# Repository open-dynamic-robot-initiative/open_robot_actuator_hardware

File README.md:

# Open Robot Actuator Hardware

**Click on the pictures below for more information**
## Electronics
| TI Evaluation Boards  | BLMC µDriver | Master Board |Details Wiring|
| ---------------  | ------------- |------------- |---|
| |   |   | |

## Mechanics
| Quadruped 8dof v2 (Solo8) | Quadruped 12dof (Solo12) | Biped 6dof (Bolt) | TriFingerEdu |
| ------------------------- | ------------- |------------- |------------- |
|||||

| 2dof Leg v2  | 3dof Leg | Biped Leg |FingerEdu |
| ------------- | ------------- |------------- |------------- |
|   |   |   |  |

| Actuator Module Core v1| Actuator Module Core v1.1 | Details 3d Printed Parts | Details Machined Parts |
| ---------------  | ------------- |------------- |------------- |
| |  | |  |

| Quadruped 12dof v1.1<br>Autonomy Upgrade | Leg Test Stand v2 | NYU Finger | Dual Motor Testbed |
| ---------------  | ------------- |------------- |-----------|
| |  |  |  |

## More Details
| Mechanical Tools and Consumables |Electronic Components and Tools| Details Electronics<br>Quadruped Robot 12dof | Lower Legs |
| --- | --- | --- |--- |
|||  |   |

| Robot Calibration | Conventions | Known Issues |  |
| --- | --- | --- | --- |
|||||

## Step-by-Step Instructions
| Motor Preparation  | Motor Shaft Preparation | Encoder Preparation |Center Pulley Preparation|
| --- | --- | --- | --- |
| |   |   | |

| Output Pulley Preparation | Shell Preparation | Actuator Module Assembly |Actuator Module Testing|
| --- | --- | --- | --- |
| |   |   | |

## Old Versions for Reference
| Quadruped 8dof v1 | 2dof Leg v1 | Leg Test Stand v1| Foot Contact Switch |
| ---------------  | ------------- |------------- |------------- |
| | |||

## More Information
[Open Dynamic Robot Initiative - Webpage](https://open-dynamic-robot-initiative.github.io)  
[Open Dynamic Robot Initiative - YouTube Channel](https://www.youtube.com/channel/UCx32JW2oIrax47Gjq8zNI-w)   
[Open Dynamic Robot Initiative - Forum](https://odri.discourse.group/categories)  
[Open Dynamic Robot Initiative - Paper](https://arxiv.org/pdf/1910.00093.pdf)  
[Hardware Overview](#open-robot-actuator-hardware)  
[Software Overview](https://github.com/open-dynamic-robot-initiative/open-dynamic-robot-initiative.github.io/wiki)  

## Authors
Jonathan Fiene  
Thomas Flayols  
Felix Grimminger  

## License
BSD 3-Clause License

## Copyright
Copyright (c) 2019-2021, Max Planck Gesellschaft and New York University

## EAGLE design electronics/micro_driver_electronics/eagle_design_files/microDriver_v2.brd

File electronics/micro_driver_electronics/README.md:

# Micro Driver Electronics

<br> <br>

* dual brushless motor driver electronics
* performs torque control at 10kHz for each motor
* miniaturized version of the [Texas Instruments Evaluation Boards](../ti_electronics/README.md#texas-instruments-evaluation-board-electronics)
* SPI communication with [Master Board](https://github.com/open-dynamic-robot-initiative/master-board#master-board) at 1kHz
* 6 layer board / FR4 / copper thickness 35μm
* Dimensions: 51mm x 50mm
* Weight: 13g
* input voltage: 5V - 32V (we operate our robots at 24V)

## LED status
GREEN/BLUE LED (shows system and motor status):<br>
Off = system disabled<br>
On =system enabled<br>
Slow Blinking = motor enabled<br>
Fast Blinking = aligning motor<br>

RED LED: Turn on if there is an error

## Motor Driver Electronics Comparison
<br> <br>

## Eagle Design Files
<br>

* [MicroDriver v2 Eagle Design Files - microDriver_v2.zip](eagle_design_files/microDriver_v2.zip)

<br><br> <br>

---
## Production Gerber Set and Assembly Packet
* [MicroDriver v2 Gerber Set - microDriver_v2_gerber.zip](production_files/microDriver_v2_gerber.zip)

* [MicroDriver v2 Assembly Packet - microDriver_v2_assembly.zip](production_files/microDriver_v2_assembly.zip)

<br><br> <br>

## Ordering Instructions
### Beta Layout
We have mostly been ordering the Micro Driver boards from [BetaLayout](https://us.beta-layout.com/pcb/).
Beta Layout has the permission to replicate our MicroDriver v2 board order for anybody who is interested - they ship worldwide.

Send an email to info.de@beta-layout.com and ask for a quote for replicating the MicroDriver v2 boards according to the order number **AU-201909/38760**.

They will send you a quote for producing the boards and for the placing and soldering service *- NOT including the cost of the electronic components.*

After you have placed the order for the boards Beta Layout will search for the components and will send you the component list with the actual component prices for your approval. For our last orders the component price was around 50€ per board.

We order the boards with all the components placed and soldered - except for the precision resistors and the Hirose connectors. The soldering of those components is described [below](#soldering-work).

### MacroFab

In the US we have also successfully ordered the Micro Driver Boards from [MacroFab](https://macrofab.com/).

---
## Bill of Materials
### Micro Driver Boards
<br> <br>

|Description|Details|Ordering Information|Comments|
|---|---|---|---|
|MicroDriver v2||[BetaLayout](https://us.beta-layout.com/pcb/)<br> USA: [MacroFab](https://macrofab.com/)|[Ordering Instructions](#ordering-instructions)|
|Precision Resistors 7mΩ ±1%|CRE2512-FZ-R007E-3|RS 824-0348<br>Mouser 652-CRE2512FZR007E-3 |Phase Current Measurement Micro Driver Board|
|Right Angle Pin Header|Pitch 2.54mm|RS 360-6364 |Motor Phase and Power Connection Micro Driver Board|
|Hirose DF13 Right Angle Header 5 Pin|DF13-5P-1.25DS(20)|Digi-Key H2202-ND|Encoder and SPI connector Micro Driver Board. We use the [right angle connectors](../details/details_components.md#hirose-df13-right-angle-pin-headers). Alternatively you can use the [straight connectors](../details/details_components.md#hirose-df13-straight-pin-headers).|

### Flash Adapter and Flash Wire
<br> <br>

|Description|Details|Ordering Information|Comments|
|---|---|---|---|
|JTAG EMULATOR XDS100V2 USB|Spectrum Digital XDS100V2 JTAG|Digi Key 702302-ND<br> Farnell 1831927||
|Pin Header 8 Position 1.27mm pitch|Amphenol ICC 20021111-00008T4LF|Digi-Key 609-3711-ND|Flash Cable Connector Micro Driver Side|
|Pin Header 2,54 mm pitch|Assmann AWL254-DG-G72A|RS 674-2347|Flash Cable Connector Emulator Side|
|Ribbon Cable|HARTING 09180107001|DigiKey 1195-4452-ND|Pitch 1,27mm / 0,050" |

---
# Soldering Work

The MicroDrivers come without any connectors (for power wires, encoders, spi and motor wires). These have to been added. In addition, six resistors have to been soldered on the back of the MicroDriver.

For the encoder connectors, it's possible to use either [Hirose DF13 Straight Pin Headers](../details/details_components.md#hirose-df13-straight-pin-headers) or the [Hirose DF13 Right Angle Pin Headers](../details/details_components.md#hirose-df13-right-angle-pin-headers)

## Resistor Soldering
The six [precision resistors](../details/details_components.md#precision-resistors) needs to be soldered on the back of the MicroDriver.<br>
**Trick:** Use some solder at the tip to initially fix the resistor a bit. Then solder the other side and fix the initial side in the end properly.

<br>

<br>

<br>

## Hirose Connector Soldering

<br>*Micro Driver Stack with right angle Hirose connectors.*<br>

We recommend to use the right angle Hirose connectors for the encoders and the SPI communication if the cards are mounted in a stack. This allows for connecting and disconnecting the encoder and SPI wires without disassembling the stack.

The **right angle Hirose connectors** are mounted to the **bottom side** of the micro driver boards as shown in the picture below.
The **straight Hirose connectors** are mounted on the **top side** of the micro driver boards. That way the pin assignment is identical and both connector options are compatible with the [Actuator Module Wiring Interface](../details/details_wiring.md#actuator-module-wiring).

<br>*Micro Driver Boards with Hirose encoder connectors.<br>Left side: right angle connectors / Right side: straight connectors*<br>

<br>*Micro Driver Boards with Hirose connector for SPI communication.<br>Left side: right angle connectors / Right side: straight connectors*<br>

<br>*Use a vise to clamp the board and locate the Hirose connector.*<br>

<br>*Solder the two encoder connectors and the spi connector onto the board.*<br>

## Motor / Power Wire Soldering

<br>*Solder a two pin right angle connector to the power terminals.*<br>

<br>*Shorten the pins, solder the extension wires and apply heat shrink.*<br>

<br>*Right angle pin and mating connector.*<br>

<br>*Use a mating connector to hold the pin during soldering.*<br>

<br>*Orient the pin as desired, apply solder and shorten the pins.*<br>

<br>*Repeat for all six motor phase connections.*<br>

<br>*Apply the extension wires and heat shrink.*<br>

<br>*Attach the [2mm motor phase connectors](../details/details_components.md#motor-phase-connectors) and label the wires.<br>On one of the boards we attach a 2 pin Hirose wire to power the Master Board.*<br>

---
## Flashing

The MicroDriver boards are flashed using a JTAG emulator connected via USB.<br> The emulator is connected to the MicroDriver using the connector cable described below.

## Wiring MicroDriver <-> JTAG Emulator

Note: A long wire might cause communication problems when attempting to flash the MicroDriver. A cable length of 10 cm worked well for us.

| Connector Emulator | Connector MicroDriver |
|--------------------|-----------------------|
|  |  |

---
## More Information
[Open Dynamic Robot Initiative - Webpage](https://open-dynamic-robot-initiative.github.io)  
[Open Dynamic Robot Initiative - YouTube Channel](https://www.youtube.com/channel/UCx32JW2oIrax47Gjq8zNI-w)  
[Open Dynamic Robot Initiative - Forum](https://odri.discourse.group/categories)  
[Open Dynamic Robot Initiative - Paper](https://arxiv.org/pdf/1910.00093.pdf)  
[Hardware Overview](../../README.md#open-robot-actuator-hardware)  
[Software Overview](https://github.com/open-dynamic-robot-initiative/open-dynamic-robot-initiative.github.io/wiki)

## Authors
* Jonathan Fiene
* Julian Viereck
* Felix Grimminger

## License
BSD 3-Clause License

## Copyright
Copyright (c) 2019-2021, Max Planck Gesellschaft and New York University

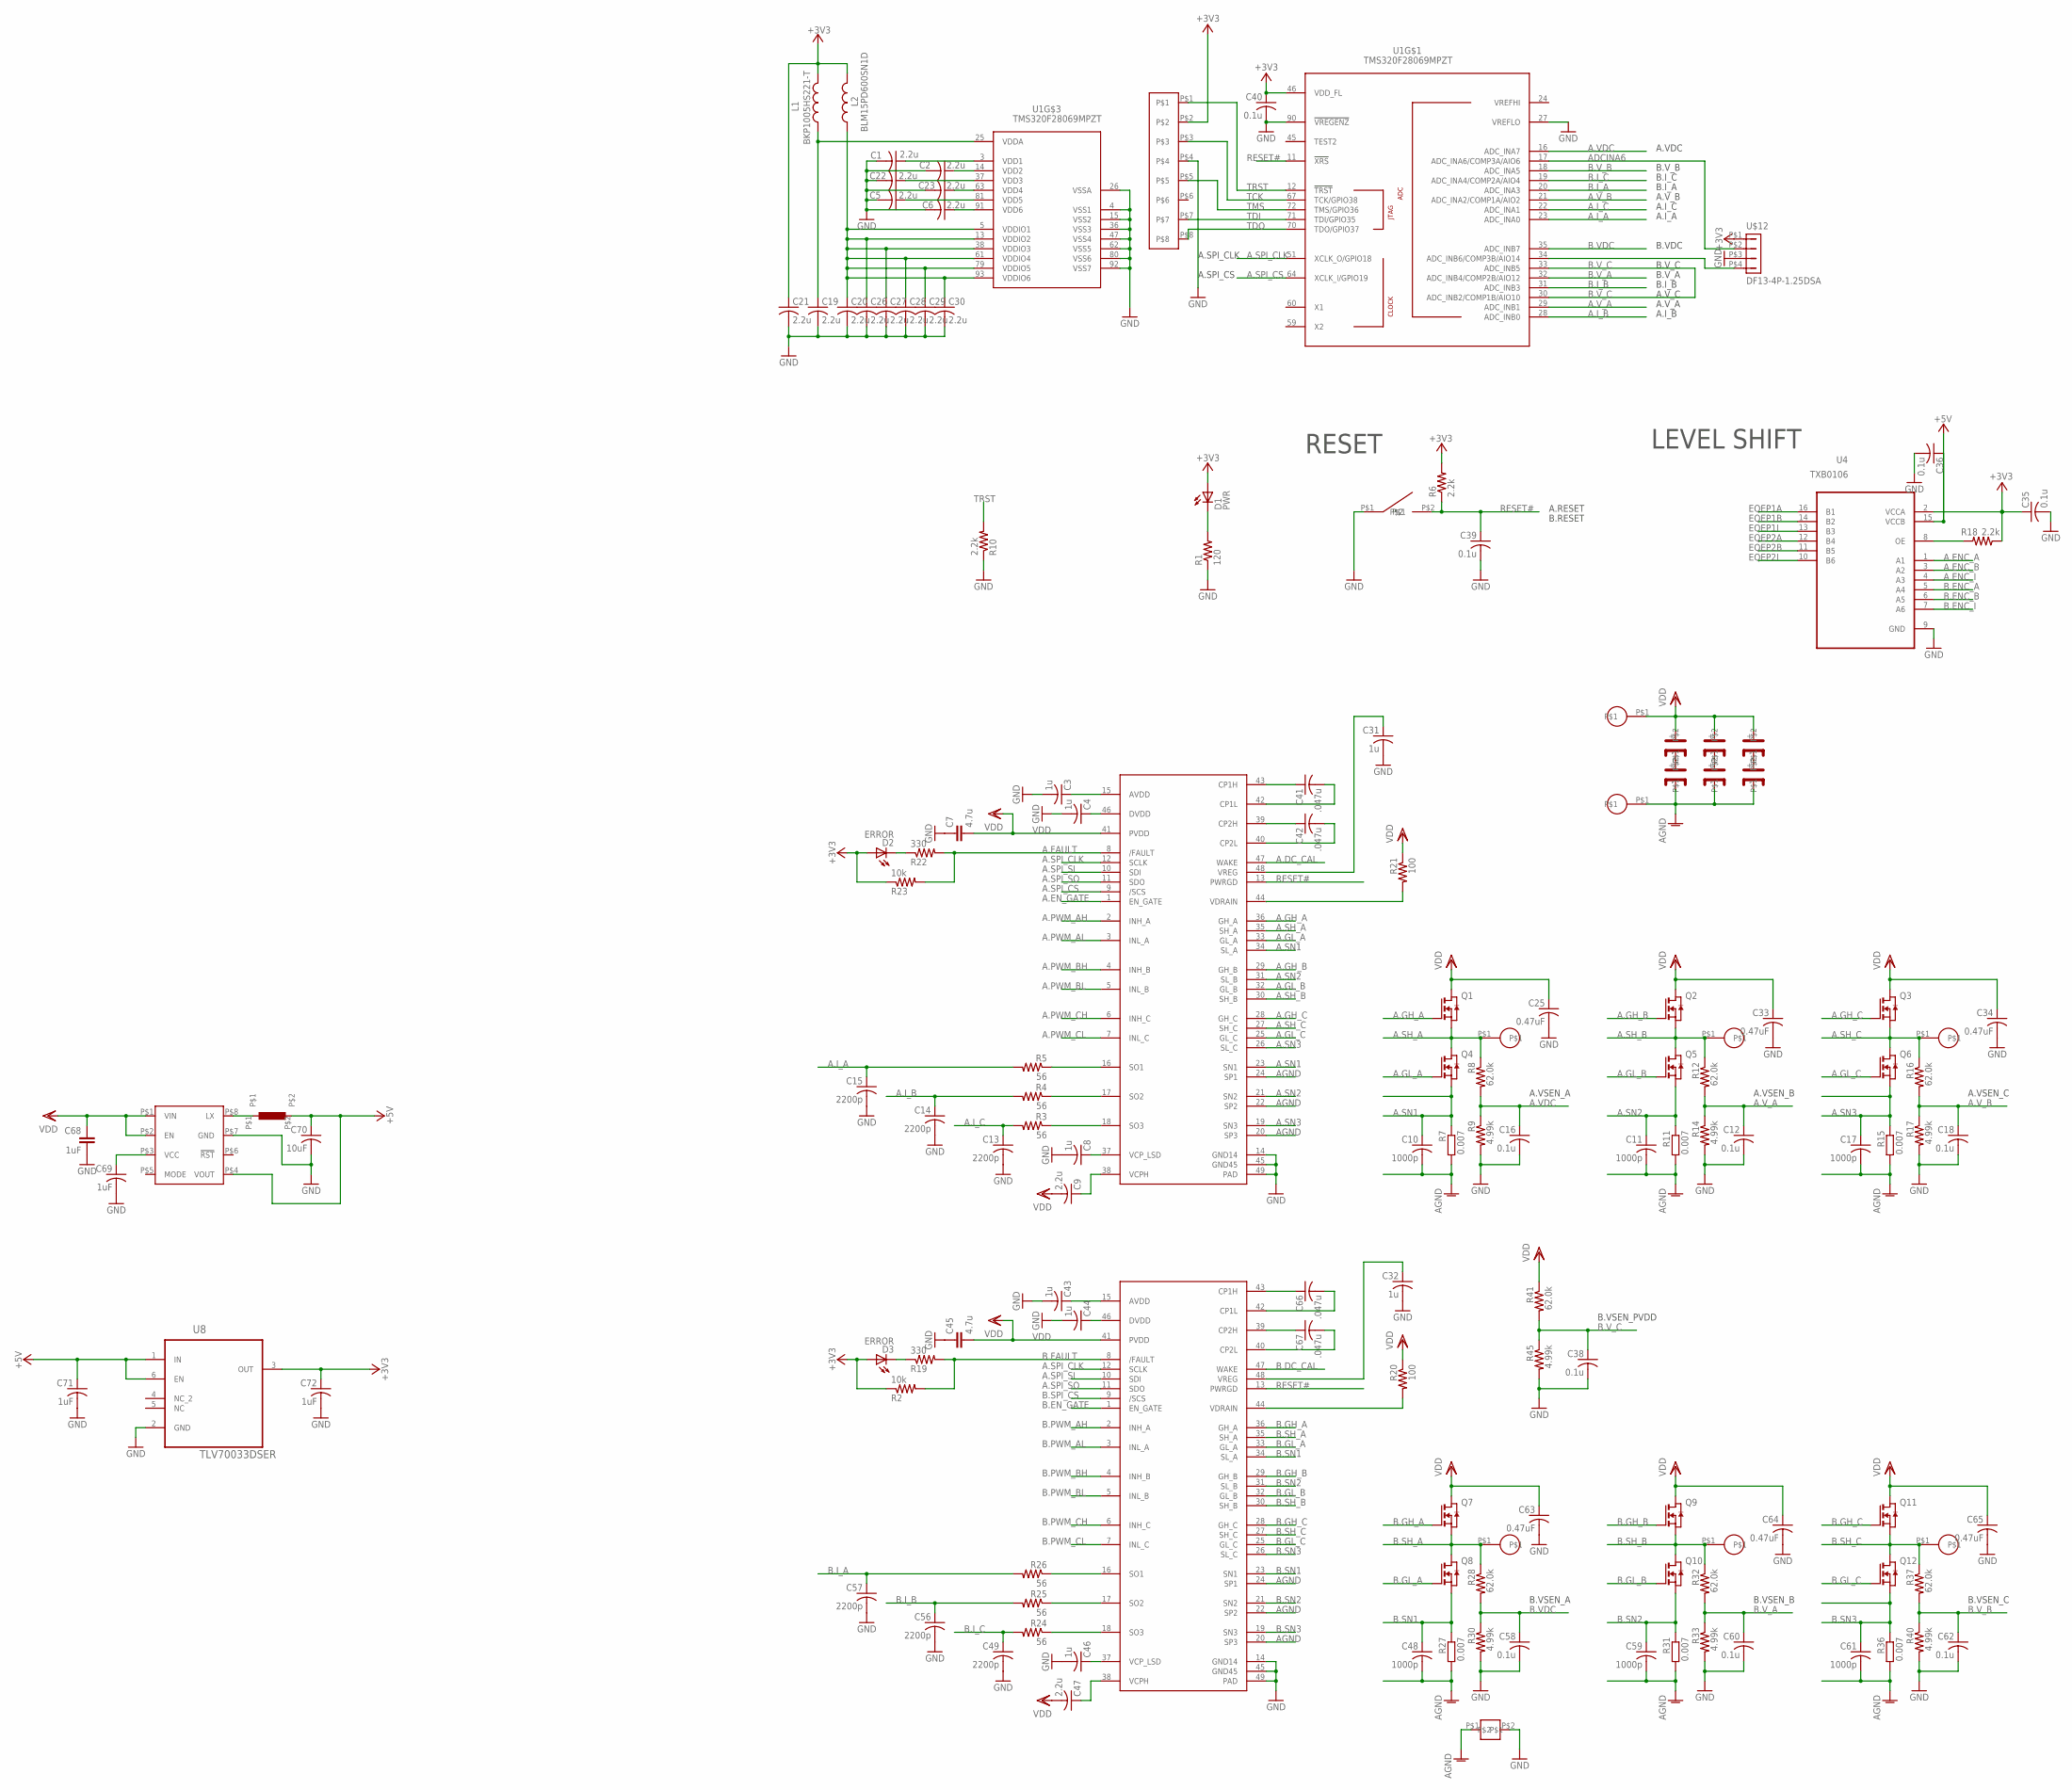
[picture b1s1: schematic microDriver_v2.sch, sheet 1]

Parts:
B1: B3U
C1, C2, C5, C6, C9, C19, C20, C21, C22, C23, C26, C27, C28, C29, C30, C47: 2.2u; C0402
C3, C4, C8, C31, C32, C43, C44, C46: 1u; C0402
C7, C45: 4.7u; C0805K
C10, C11, C17, C48, C59, C61: 1000p; C0402
C12, C16, C18, C35, C36, C38, C39, C40, C58, C60, C62: 0.1u; C0402
C13, C14, C15, C49, C56, C57: 2200p; C0402
C25, C33, C34, C63, C64, C65: 0.47uF; C0402
C41, C42, C66, C67: .047u; C0402
C68: 1uF; C0603
C69, C71, C72: 1uF; C0402
C70: 10uF; C0402
D1: PWR; CHIP-LED0603
D2, D3: ERROR; CHIP-LED0603
I1: NR4018; 4X4
L1: BKP1005HS221-T; R0402
L2: BLM15PD600SN1D; R0402
M1: AMP-8; AMP-MINITEK-8
Q1, Q2, Q3, Q4, Q5, Q6, Q7, Q8, Q9, Q10, Q11, Q12: CSD18540; Q5B
R1: 120; R0402
R2, R23: 10k; R0402
R3, R4, R5, R24, R25, R26: 56; R0402
R6, R10, R18: 2.2k; R0402
R7, R11, R15, R27, R31, R36: 0.007; R2512
R8, R12, R16, R28, R32, R37, R41: 62.0k; R0402
R9, R14, R17, R30, R33, R40, R45: 4.99k; R0402
R19, R22: 330; R0402
R20, R21: 100; R0402
T1, T2, T3, T4, T5, T6: 7343-CAP; M7343-CAP
U1: TMS320F28069MPZT; PQFP100
U4: TXB0106; VQFN-N16
U5, U6: DRV8305; HTQFP-48
U7: MAX15062; TDFN-8
U8: TLV70033DSER; SON50P150X150X80-6N
U$2: GND-AGND
U$3, U$4, U$5, U$6, U$7, U$8, U$9, U$10: BLDC_PAD
U$12: DF13-4P-1.25DSA

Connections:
+3V3: C21.1, C35.1, C40.1, C72.1, D1.A, D2.A, D3.A, L1.2, L2.2, M1.P$2, R2.1, R6.2, R18.1, R23.1, U1.46 (VDD_FL), U4.2 (VCCA), U8.3 (OUT), U$12.P$1 (1); also elsewhere on the board
+5V: C36.1, C70.1, C71.1, I1.P$2, U4.15 (VCCB), U7.P$4 (VOUT), U8.1 (IN), U8.6 (EN); also elsewhere on the board
A.DC_CAL: U6.47 (WAKE); also elsewhere on the board
A.ENC_A: U4.1 (A1); also elsewhere on the board
A.ENC_B: U4.3 (A2); also elsewhere on the board
A.ENC_I: U4.4 (A3); also elsewhere on the board
A.EN_GATE: U6.1 (EN_GATE); also elsewhere on the board
A.FAULT: R22.2, R23.2, U6.8 (/FAULT); also elsewhere on the board
A.GH_A: Q1.4 (G), U6.36 (GH_A)
A.GH_B: Q2.4 (G), U6.29 (GH_B)
A.GH_C: Q3.4 (G), U6.28 (GH_C)
A.GL_A: Q4.4 (G), U6.33 (GL_A)
A.GL_B: Q5.4 (G), U6.32 (GL_B)
A.GL_C: Q6.4 (G), U6.25 (GL_C)
A.I_A: C15.1, R5.2, U1.23 (ADC_INA0)
A.I_B: C14.1, R4.2, U1.28 (ADC_INB0)
A.I_C: C13.1, R3.2, U1.22 (ADC_INA1)
A.PWM_AH: U6.2 (INH_A); also elsewhere on the board
A.PWM_AL: U6.3 (INL_A); also elsewhere on the board
A.PWM_BH: U6.4 (INH_B); also elsewhere on the board
A.PWM_BL: U6.5 (INL_B); also elsewhere on the board
A.PWM_CH: U6.6 (INH_C); also elsewhere on the board
A.PWM_CL: U6.7 (INL_C); also elsewhere on the board
A.SH_A: Q1.1 (S), Q1.2 (S), Q1.3 (S), Q4.5 (D), Q4.6 (D), Q4.7 (D), Q4.8 (D), Q4.9 (D), R8.1, U6.35 (SH_A), U$6.P$1
A.SH_B: Q2.1 (S), Q2.2 (S), Q2.3 (S), Q5.5 (D), Q5.6 (D), Q5.7 (D), Q5.8 (D), Q5.9 (D), R12.1, U6.30 (SH_B), U$7.P$1
A.SH_C: Q3.1 (S), Q3.2 (S), Q3.3 (S), Q6.5 (D), Q6.6 (D), Q6.7 (D), Q6.8 (D), Q6.9 (D), R16.1, U6.27 (SH_C), U$8.P$1
A.SN1: C10.1, Q4.1 (S), Q4.2 (S), Q4.3 (S), R7.1, U6.23 (SN1), U6.34 (SL_A)
A.SN2: C11.1, Q5.1 (S), Q5.2 (S), Q5.3 (S), R11.1, U6.21 (SN2), U6.31 (SL_B)
A.SN3: C17.1, Q6.1 (S), Q6.2 (S), Q6.3 (S), R15.1, U6.19 (SN3), U6.26 (SL_C)
A.SPI_CLK: U1.51 (XCLK_O/GPIO18), U5.12 (SCLK), U6.12 (SCLK); also elsewhere on the board
A.SPI_CS: U1.64 (XCLK_I/GPIO19), U6.9 (/SCS)
A.SPI_SI: U5.10 (SDI), U6.10 (SDI); also elsewhere on the board
A.SPI_SO: U5.11 (SDO), U6.11 (SDO); also elsewhere on the board
A.VDC: C16.1, R8.2, R9.1, U1.16 (ADC_INA7)
A.V_A: C12.1, R12.2, R14.1, U1.29 (ADC_INB1)
A.V_B: C18.1, R16.2, R17.1, U1.21 (ADC_INA2/COMP1A/AIO2)
ADCINA6: U1.17 (ADC_INA6/COMP3A/AIO6), U$12.P$2 (2)
AGND: C10.2, C11.2, C17.2, C48.2, C59.2, C61.2, R7.2, R11.2, R15.2, R27.2, R31.2, R36.2, T2.-, T4.-, T6.-, U5.20 (SP3), U5.22 (SP2), U5.24 (SP1), U6.20 (SP3), U6.22 (SP2), U6.24 (SP1), U$2.P$1, U$10.P$1
AVDD: C3.1, U6.15 (AVDD)
AVDD1: C43.1, U5.15 (AVDD)
B.DC_CAL: U5.47 (WAKE); also elsewhere on the board
B.ENC_A: U4.5 (A4); also elsewhere on the board
B.ENC_B: U4.6 (A5); also elsewhere on the board
B.ENC_I: U4.7 (A6); also elsewhere on the board
B.EN_GATE: U5.1 (EN_GATE); also elsewhere on the board
B.FAULT: R2.2, R19.2, U5.8 (/FAULT); also elsewhere on the board
B.GH_A: Q7.4 (G), U5.36 (GH_A)
B.GH_B: Q9.4 (G), U5.29 (GH_B)
B.GH_C: Q11.4 (G), U5.28 (GH_C)
B.GL_A: Q8.4 (G), U5.33 (GL_A)
B.GL_B: Q10.4 (G), U5.32 (GL_B)
B.GL_C: Q12.4 (G), U5.25 (GL_C)
B.I_A: C57.1, R26.2, U1.20 (ADC_INA3)
B.I_B: C56.1, R25.2, U1.31 (ADC_INB3)
B.I_C: C49.1, R24.2, U1.19 (ADC_INA4/COMP2A/AIO4)
B.PWM_AH: U5.2 (INH_A); also elsewhere on the board
B.PWM_AL: U5.3 (INL_A); also elsewhere on the board
B.PWM_BH: U5.4 (INH_B); also elsewhere on the board
B.PWM_BL: U5.5 (INL_B); also elsewhere on the board
B.PWM_CH: U5.6 (INH_C); also elsewhere on the board
B.PWM_CL: U5.7 (INL_C); also elsewhere on the board
B.SH_A: Q7.1 (S), Q7.2 (S), Q7.3 (S), Q8.5 (D), Q8.6 (D), Q8.7 (D), Q8.8 (D), Q8.9 (D), R28.1, U5.35 (SH_A), U$3.P$1
B.SH_B: Q9.1 (S), Q9.2 (S), Q9.3 (S), Q10.5 (D), Q10.6 (D), Q10.7 (D), Q10.8 (D), Q10.9 (D), R32.1, U5.30 (SH_B), U$4.P$1
B.SH_C: Q11.1 (S), Q11.2 (S), Q11.3 (S), Q12.5 (D), Q12.6 (D), Q12.7 (D), Q12.8 (D), Q12.9 (D), R37.1, U5.27 (SH_C), U$5.P$1
B.SN1: C48.1, Q8.1 (S), Q8.2 (S), Q8.3 (S), R27.1, U5.23 (SN1), U5.34 (SL_A)
B.SN2: C59.1, Q10.1 (S), Q10.2 (S), Q10.3 (S), R31.1, U5.21 (SN2), U5.31 (SL_B)
B.SN3: C61.1, Q12.1 (S), Q12.2 (S), Q12.3 (S), R36.1, U5.19 (SN3), U5.26 (SL_C)
B.SPI_CS: U5.9 (/SCS); also elsewhere on the board
B.VDC: C58.1, R28.2, R30.1, U1.35 (ADC_INB7)
B.V_A: C60.1, R32.2, R33.1, U1.32 (ADC_INB4/COMP2B/AIO12)
B.V_B: C62.1, R37.2, R40.1, U1.18 (ADC_INA5)
B.V_C: C38.1, R41.2, R45.1, U1.30 (ADC_INB2/COMP1B/AIO10), U1.33 (ADC_INB5)
EQEP1A: U4.16 (B1); also elsewhere on the board
EQEP1B: U4.14 (B2); also elsewhere on the board
EQEP1I: U4.13 (B3); also elsewhere on the board
EQEP2A: U4.12 (B4); also elsewhere on the board
EQEP2B: U4.11 (B5); also elsewhere on the board
EQEP2I: U4.10 (B6); also elsewhere on the board
GND: B1.P$1, C1.2, C2.2, C3.2, C4.2, C5.2, C6.2, C7.1, C8.2, C12.2, C13.2, C14.2, C15.2, C16.2, C18.2, C19.2, C20.2, C21.2, C22.2, C23.2, C25.2, C26.2, C27.2, C28.2, C29.2, C30.2, C31.2, C32.2, C33.2, C34.2, C35.2, C36.2, C38.2, C39.2, C40.2, C43.2, C44.2, C45.1, C46.2, C49.2, C56.2, C57.2, C58.2, C60.2, C62.2, C63.2, C64.2, C65.2, C68.2, C69.2, C70.2, C71.2, C72.2, M1.P$4, R1.1, R9.2, R10.1, R14.2, R17.2, R30.2, R33.2, R40.2, R45.2, U1.4 (VSS1), U1.15 (VSS2), U1.26 (VSSA), U1.27 (VREFLO), U1.36 (VSS3), U1.47 (VSS4), U1.62 (VSS5), U1.80 (VSS6), U1.90 (!VREGENZ), U1.92 (VSS7), U4.9 (GND), U5.14 (GND14), U5.45 (GND45), U5.49 (PAD), U6.14 (GND14), U6.45 (GND45), U6.49 (PAD), U7.P$7 (GND), U8.2 (GND), U$2.P$2, U$12.P$3 (3); also elsewhere on the board
unnamed: U1.34 (ADC_INB6/COMP3B/AIO14), U$12.P$4 (4)
unnamed: C4.1, U6.46 (DVDD)
unnamed: R3.1, U6.18 (SO3)
unnamed: C8.1, U6.37 (VCP_LSD)
unnamed: C9.1, U6.38 (VCPH)
unnamed: C41.1, U6.43 (CP1H)
unnamed: R4.1, U6.17 (SO2)
unnamed: R5.1, U6.16 (SO1)
unnamed: C42.1, U6.39 (CP2H)
unnamed: C41.2, U6.42 (CP1L)
unnamed: C42.2, U6.40 (CP2L)
unnamed: R18.2, U4.8 (OE)
unnamed: D2.C, R22.1
unnamed: R21.2, U6.44 (VDRAIN)
unnamed: C44.1, U5.46 (DVDD)
unnamed: C46.1, U5.37 (VCP_LSD)
unnamed: C32.1, U5.48 (VREG)
unnamed: R24.1, U5.18 (SO3)
unnamed: C47.1, U5.38 (VCPH)
unnamed: R25.1, U5.17 (SO2)
unnamed: R26.1, U5.16 (SO1)
unnamed: C66.1, U5.43 (CP1H)
unnamed: C67.1, U5.39 (CP2H)
unnamed: C66.2, U5.42 (CP1L)
unnamed: C67.2, U5.40 (CP2L)
unnamed: D1.C, R1.2
unnamed: C1.1, U1.3 (VDD1)
unnamed: C2.1, U1.14 (VDD2)
unnamed: C22.1, U1.37 (VDD3)
unnamed: C23.1, U1.63 (VDD4)
unnamed: T1.-, T2.+
unnamed: T3.-, T4.+
unnamed: R20.2, U5.44 (VDRAIN)
unnamed: C5.1, U1.81 (VDD5)
unnamed: C6.1, U1.91 (VDD6)
unnamed: D3.C, R19.1
unnamed: T5.-, T6.+
unnamed: C31.1, U6.48 (VREG)
unnamed: I1.P$1, U7.P$8 (LX)
unnamed: C69.1, U7.P$3 (VCC)
RESET#: B1.P$2, C39.1, R6.1, U1.11 (!XRS), U5.13 (PWRGD), U6.13 (PWRGD)
TCK: M1.P$3, U1.67 (TCK/GPIO38)
TDI: M1.P$7, U1.71 (TDI/GPIO35)
TDO: M1.P$8, U1.70 (TDO/GPIO37)
TMS: M1.P$5, U1.72 (TMS/GPIO36)
TRST: M1.P$1, R10.2, U1.12 (!TRST)
VDD: C7.2, C9.2, C25.1, C33.1, C34.1, C45.2, C47.2, C63.1, C64.1, C65.1, C68.1, Q1.5 (D), Q1.6 (D), Q1.7 (D), Q1.8 (D), Q1.9 (D), Q2.5 (D), Q2.6 (D), Q2.7 (D), Q2.8 (D), Q2.9 (D), Q3.5 (D), Q3.6 (D), Q3.7 (D), Q3.8 (D), Q3.9 (D), Q7.5 (D), Q7.6 (D), Q7.7 (D), Q7.8 (D), Q7.9 (D), Q9.5 (D), Q9.6 (D), Q9.7 (D), Q9.8 (D), Q9.9 (D), Q11.5 (D), Q11.6 (D), Q11.7 (D), Q11.8 (D), Q11.9 (D), R20.1, R21.1, R41.1, T1.+, T3.+, T5.+, U5.41 (PVDD), U6.41 (PVDD), U7.P$1 (VIN), U7.P$2 (EN), U$9.P$1
VDDA: C19.1, L1.1, U1.25 (VDDA)
VDDIO: C20.1, C26.1, C27.1, C28.1, C29.1, C30.1, L2.1, U1.5 (VDDIO1), U1.13 (VDDIO2), U1.38 (VDDIO3), U1.61 (VDDIO4), U1.79 (VDDIO5), U1.93 (VDDIO6)

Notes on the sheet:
RESET
A.SPI_CLK
A.SPI_CS
A.RESET
B.RESET
B.VDC
B.V_A
B.V_B
B.V_C
B.I_A
B.I_B
B.I_C
A.VDC
A.V_A
A.V_B
A.V_C
A.I_A
A.I_B
A.I_C
A.VSEN_A
A.VSEN_B
A.VSEN_C
B.VSEN_A
B.VSEN_B
B.VSEN_C
B.VSEN_PVDD
LEVEL SHIFT

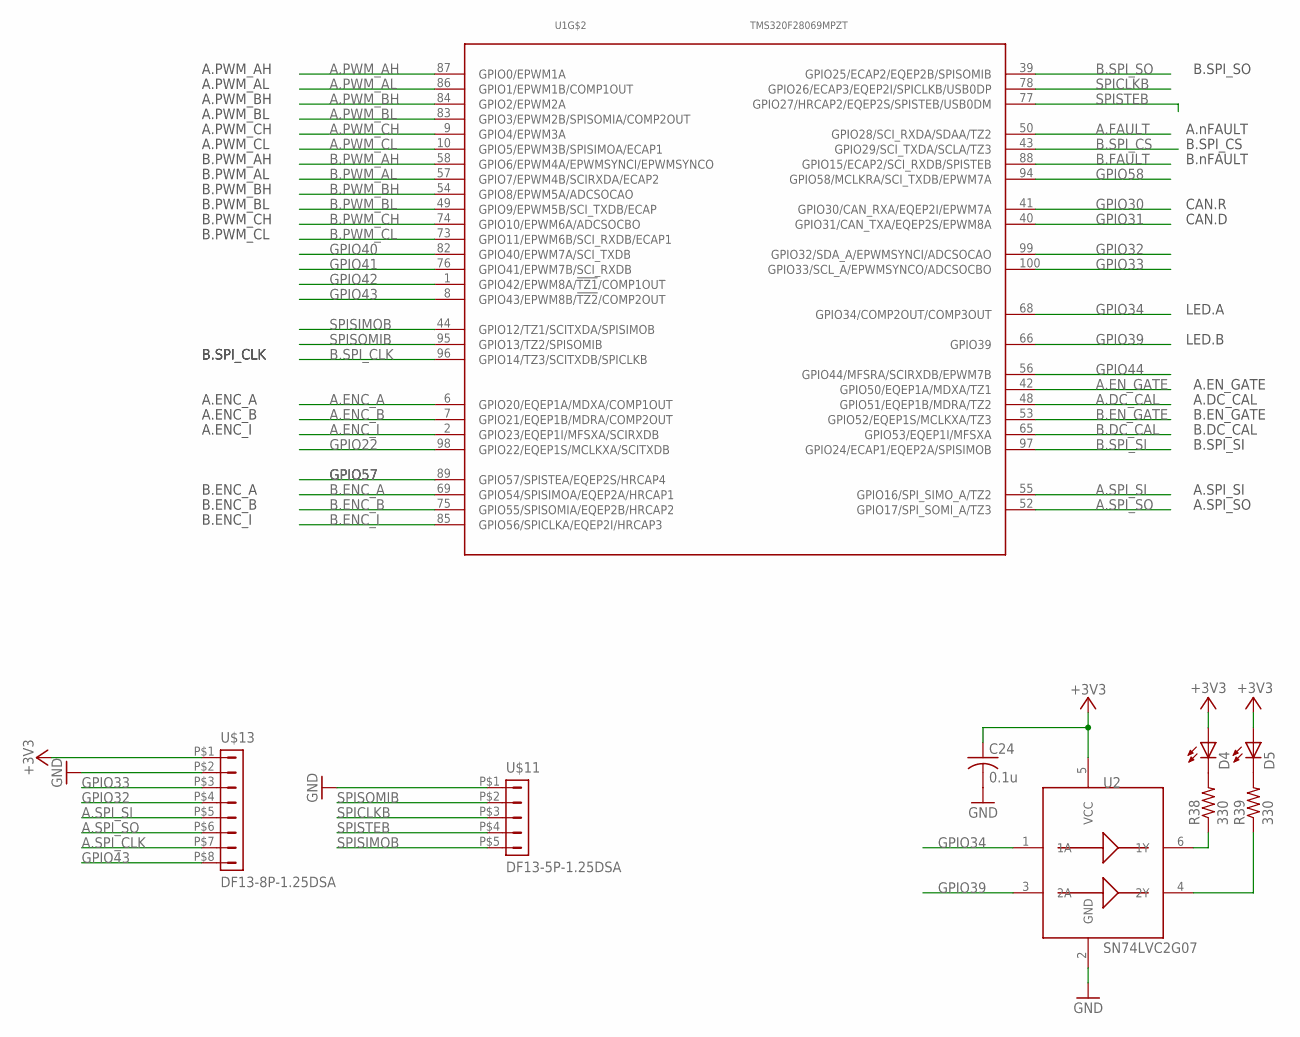
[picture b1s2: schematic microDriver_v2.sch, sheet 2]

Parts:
C24: 0.1u; C0402
D4, D5: LEDCHIP-LED0603; CHIP-LED0603
R38, R39: 330; R0402
U1: TMS320F28069MPZT; PQFP100
U2: SN74LVC2G07; SOT23-6-DBV
U$11: DF13-5P-1.25DSA
U$13: DF13-8P-1.25DSA

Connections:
+3V3: C24.1, D4.A, D5.A, U2.5 (VCC), U$13.P$1 (1); also elsewhere on the board
A.DC_CAL: U1.48 (GPIO51/EQEP1B/MDRA/TZ2); also elsewhere on the board
A.ENC_A: U1.6 (GPIO20/EQEP1A/MDXA/COMP1OUT); also elsewhere on the board
A.ENC_B: U1.7 (GPIO21/EQEP1B/MDRA/COMP2OUT); also elsewhere on the board
A.ENC_I: U1.2 (GPIO23/EQEP1I/MFSXA/SCIRXDB); also elsewhere on the board
A.EN_GATE: U1.42 (GPIO50/EQEP1A/MDXA/TZ1); also elsewhere on the board
A.FAULT: U1.50 (GPIO28/SCI_RXDA/SDAA/TZ2); also elsewhere on the board
A.PWM_AH: U1.87 (GPIO0/EPWM1A); also elsewhere on the board
A.PWM_AL: U1.86 (GPIO1/EPWM1B/COMP1OUT); also elsewhere on the board
A.PWM_BH: U1.84 (GPIO2/EPWM2A); also elsewhere on the board
A.PWM_BL: U1.83 (GPIO3/EPWM2B/SPISOMIA/COMP2OUT); also elsewhere on the board
A.PWM_CH: U1.9 (GPIO4/EPWM3A); also elsewhere on the board
A.PWM_CL: U1.10 (GPIO5/EPWM3B/SPISIMOA/ECAP1); also elsewhere on the board
A.SPI_CLK: U$13.P$7 (7); also elsewhere on the board
A.SPI_SI: U1.55 (GPIO16/SPI_SIMO_A/TZ2), U$13.P$5 (5); also elsewhere on the board
A.SPI_SO: U1.52 (GPIO17/SPI_SOMI_A/TZ3), U$13.P$6 (6); also elsewhere on the board
B.DC_CAL: U1.65 (GPIO53/EQEP1I/MFSXA); also elsewhere on the board
B.ENC_A: U1.69 (GPIO54/SPISIMOA/EQEP2A/HRCAP1); also elsewhere on the board
B.ENC_B: U1.75 (GPIO55/SPISOMIA/EQEP2B/HRCAP2); also elsewhere on the board
B.ENC_I: U1.85 (GPIO56/SPICLKA/EQEP2I/HRCAP3); also elsewhere on the board
B.EN_GATE: U1.53 (GPIO52/EQEP1S/MCLKXA/TZ3); also elsewhere on the board
B.FAULT: U1.88 (GPIO15/ECAP2/SCI_RXDB/SPISTEB); also elsewhere on the board
B.PWM_AH: U1.58 (GPIO6/EPWM4A/EPWMSYNCI/EPWMSYNCO); also elsewhere on the board
B.PWM_AL: U1.57 (GPIO7/EPWM4B/SCIRXDA/ECAP2); also elsewhere on the board
B.PWM_BH: U1.54 (GPIO8/EPWM5A/ADCSOCAO); also elsewhere on the board
B.PWM_BL: U1.49 (GPIO9/EPWM5B/SCI_TXDB/ECAP); also elsewhere on the board
B.PWM_CH: U1.74 (GPIO10/EPWM6A/ADCSOCBO); also elsewhere on the board
B.PWM_CL: U1.73 (GPIO11/EPWM6B/SCI_RXDB/ECAP1); also elsewhere on the board
B.SPI_CLK: U1.96 (GPIO14/TZ3/SCITXDB/SPICLKB)
B.SPI_CS: U1.43 (GPIO29/SCI_TXDA/SCLA/TZ3); also elsewhere on the board
B.SPI_SI: U1.97 (GPIO24/ECAP1/EQEP2A/SPISIMOB)
B.SPI_SO: U1.39 (GPIO25/ECAP2/EQEP2B/SPISOMIB)
GND: C24.2, U2.2 (GND), U$11.P$1 (1), U$13.P$2 (2); also elsewhere on the board
GPIO22: U1.98 (GPIO22/EQEP1S/MCLKXA/SCITXDB)
GPIO30: U1.41 (GPIO30/CAN_RXA/EQEP2I/EPWM7A); also elsewhere on the board
GPIO31: U1.40 (GPIO31/CAN_TXA/EQEP2S/EPWM8A); also elsewhere on the board
GPIO32: U1.99 (GPIO32/SDA_A/EPWMSYNCI/ADCSOCAO), U$13.P$4 (4)
GPIO33: U1.100 (GPIO33/SCL_A/EPWMSYNCO/ADCSOCBO), U$13.P$3 (3)
GPIO34: U1.68 (GPIO34/COMP2OUT/COMP3OUT), U2.1 (1A)
GPIO39: U1.66 (GPIO39), U2.3 (2A)
GPIO40: U1.82 (GPIO40/EPWM7A/SCI_TXDB)
GPIO41: U1.76 (GPIO41/EPWM7B/SCI_RXDB)
GPIO42: U1.1 (GPIO42/EPWM8A/!TZ1!/COMP1OUT)
GPIO43: U1.8 (GPIO43/EPWM8B/!TZ2!/COMP2OUT), U$13.P$8 (8)
GPIO44: U1.56 (GPIO44/MFSRA/SCIRXDB/EPWM7B)
GPIO57: U1.89 (GPIO57/SPISTEA/EQEP2S/HRCAP4)
GPIO58: U1.94 (GPIO58/MCLKRA/SCI_TXDB/EPWM7A)
unnamed: D4.C, R38.2
unnamed: D5.C, R39.2
unnamed: R38.1, U2.6 (1Y)
unnamed: R39.1, U2.4 (2Y)
SPICLKB: U1.78 (GPIO26/ECAP3/EQEP2I/SPICLKB/USB0DP), U$11.P$3 (3)
SPISIMOB: U1.44 (GPIO12/TZ1/SCITXDA/SPISIMOB), U$11.P$5 (5)
SPISOMIB: U1.95 (GPIO13/TZ2/SPISOMIB), U$11.P$2 (2)
SPISTEB: U1.77 (GPIO27/HRCAP2/EQEP2S/SPISTEB/USB0DM), U$11.P$4 (4)

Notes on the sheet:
A.nFAULT
B.nFAULT
B.SPI_CLK
B.PWM_AH
B.PWM_AL
B.PWM_BH
B.PWM_BL
B.PWM_CH
B.PWM_CL
A.PWM_AH
A.PWM_AL
A.PWM_BH
A.PWM_BL
A.PWM_CH
A.PWM_CL
B.SPI_CS
B.SPI_SI
B.SPI_SO
B.EN_GATE
B.DC_CAL
A.EN_GATE
A.DC_CAL
A.SPI_SI
A.SPI_SO
A.ENC_A
A.ENC_B
A.ENC_I
B.ENC_A
B.ENC_B
B.ENC_I
CAN.R
CAN.D
LED.A
LED.B

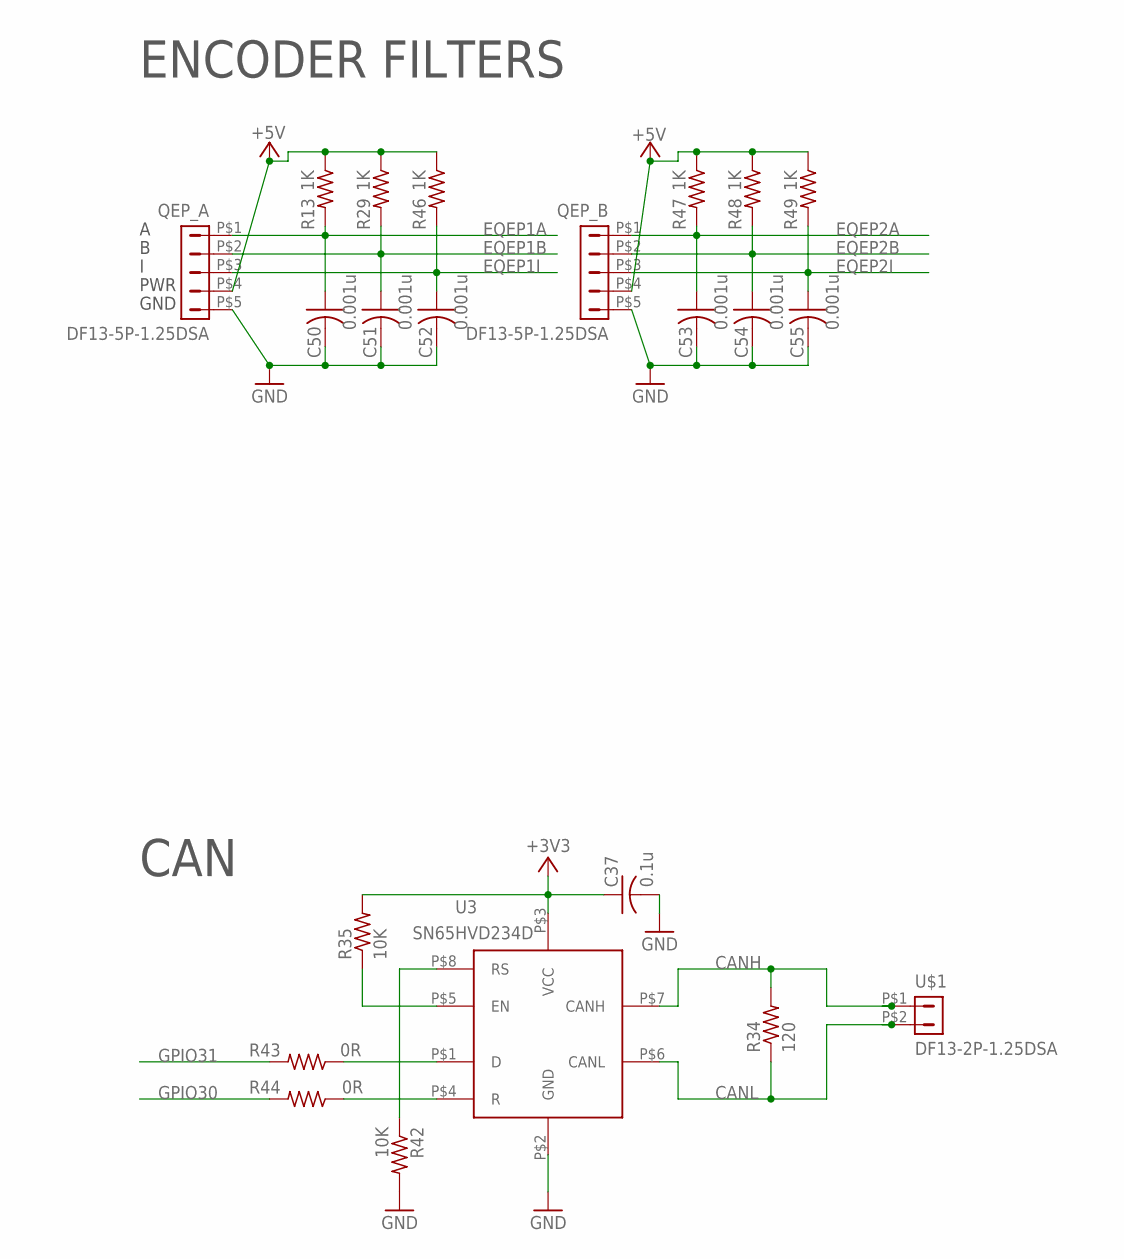
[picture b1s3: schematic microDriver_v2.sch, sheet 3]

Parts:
C37: 0.1u; C0402
C50, C51, C52, C53, C54, C55: 0.001u; C0402
QEP_A: DF13-5P-1.25DSA
QEP_B: DF13-5P-1.25DSA
R13, R29, R46, R47, R48, R49: 1K; R0402
R34: 120; R0402
R35, R42: 10K; R0402
R43, R44: 0R; R0402
U3: SN65HVD234D; SOIC8-PDSO
U$1: DF13-2P-1.25DSA

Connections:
+3V3: C37.1, R35.2, U3.P$3 (VCC); also elsewhere on the board
+5V: QEP_A.P$4 (4), QEP_B.P$4 (4), R13.1, R29.1, R46.1, R47.1, R48.1, R49.1; also elsewhere on the board
CANH: R34.2, U3.P$7 (CANH), U$1.P$1 (1)
CANL: R34.1, U3.P$6 (CANL), U$1.P$2 (2)
EQEP1A: C50.1, QEP_A.P$1 (1), R13.2; also elsewhere on the board
EQEP1B: C51.1, QEP_A.P$2 (2), R29.2; also elsewhere on the board
EQEP1I: C52.1, QEP_A.P$3 (3), R46.2; also elsewhere on the board
EQEP2A: C53.1, QEP_B.P$1 (1), R47.2; also elsewhere on the board
EQEP2B: C54.1, QEP_B.P$2 (2), R48.2; also elsewhere on the board
EQEP2I: C55.1, QEP_B.P$3 (3), R49.2; also elsewhere on the board
GND: C37.2, C50.2, C51.2, C52.2, C53.2, C54.2, C55.2, QEP_A.P$5 (5), QEP_B.P$5 (5), R42.2, U3.P$2 (GND); also elsewhere on the board
GPIO30: R44.2; also elsewhere on the board
GPIO31: R43.2; also elsewhere on the board
unnamed: R35.1, U3.P$5 (EN)
unnamed: R42.1, U3.P$8 (RS)
unnamed: R43.1, U3.P$1 (D)
unnamed: R44.1, U3.P$4 (R)

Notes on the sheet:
GND
PWR
CAN
ENCODER FILTERS

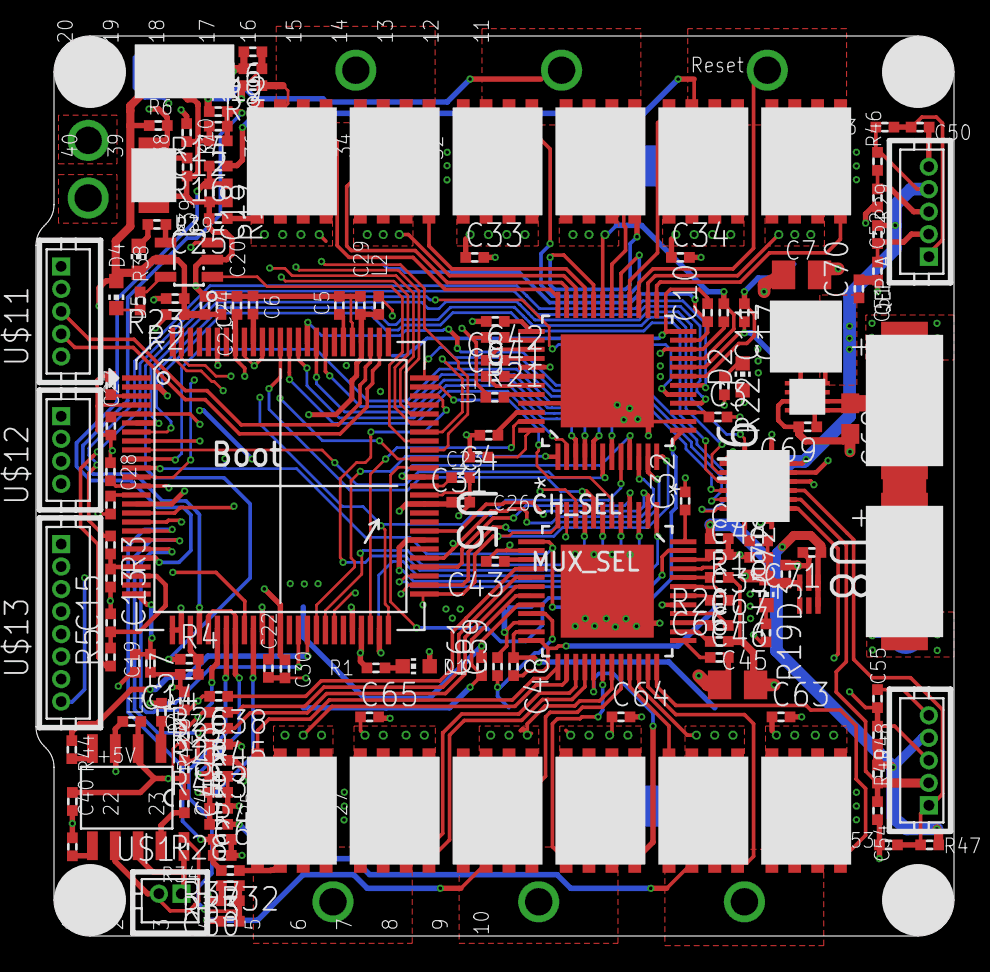
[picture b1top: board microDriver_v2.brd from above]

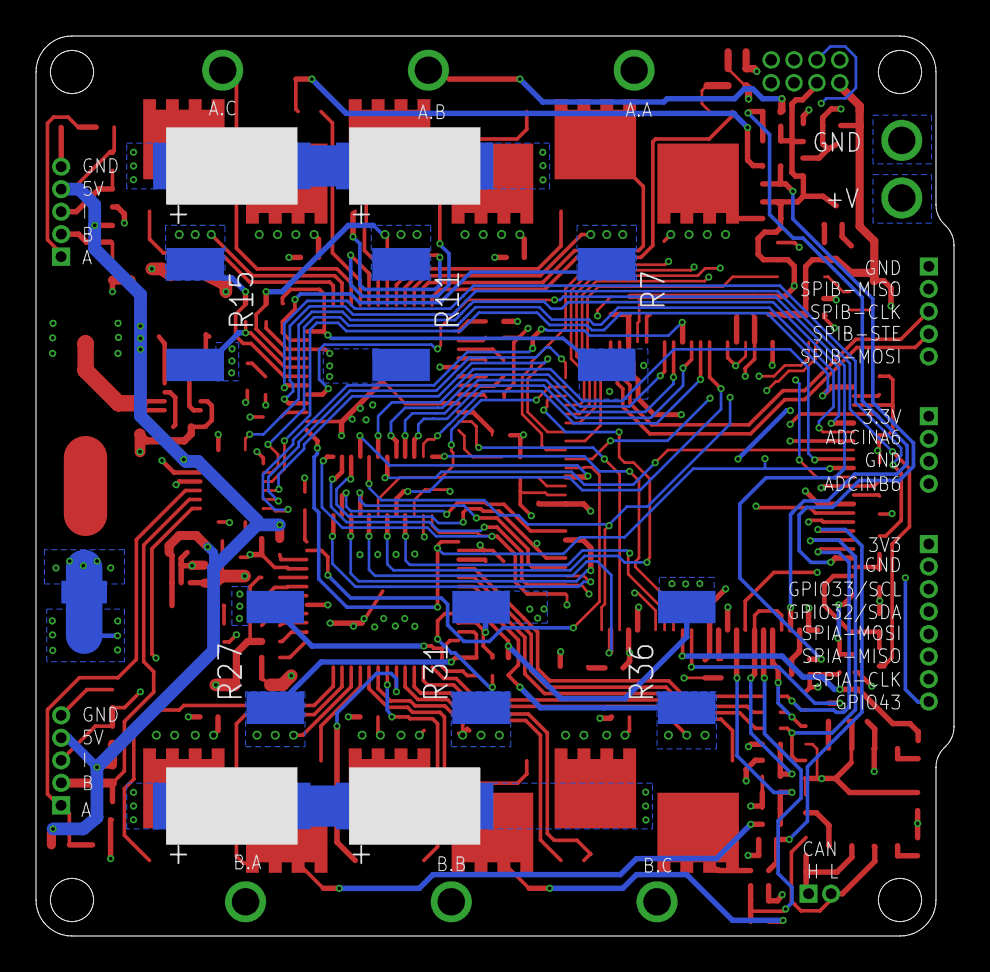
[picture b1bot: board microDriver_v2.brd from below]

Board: 6 copper layers, 51.0 x 50.0 mm, 172 parts (11 on the bottom side), 149 nets.
